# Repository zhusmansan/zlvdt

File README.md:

# Микроконтроллерный (esp32) преобразователь LVDT -> modbus 

Устройство для считывания LVDT сигнала с линейного датчика перемещений и передачи данных по modbus.

## Железо

Схема усилителя в папке [zlvdt_pcb](./zlvdt_pcb). 
Kicad проект.

## Софт

ESP_IDF проект прошивки в папке [zlvdt_firmware](./zlvdt_firmware)

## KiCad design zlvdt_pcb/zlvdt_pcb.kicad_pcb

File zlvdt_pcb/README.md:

# Усилитель и прецизионный выпрямитель для LVDT сигнала.

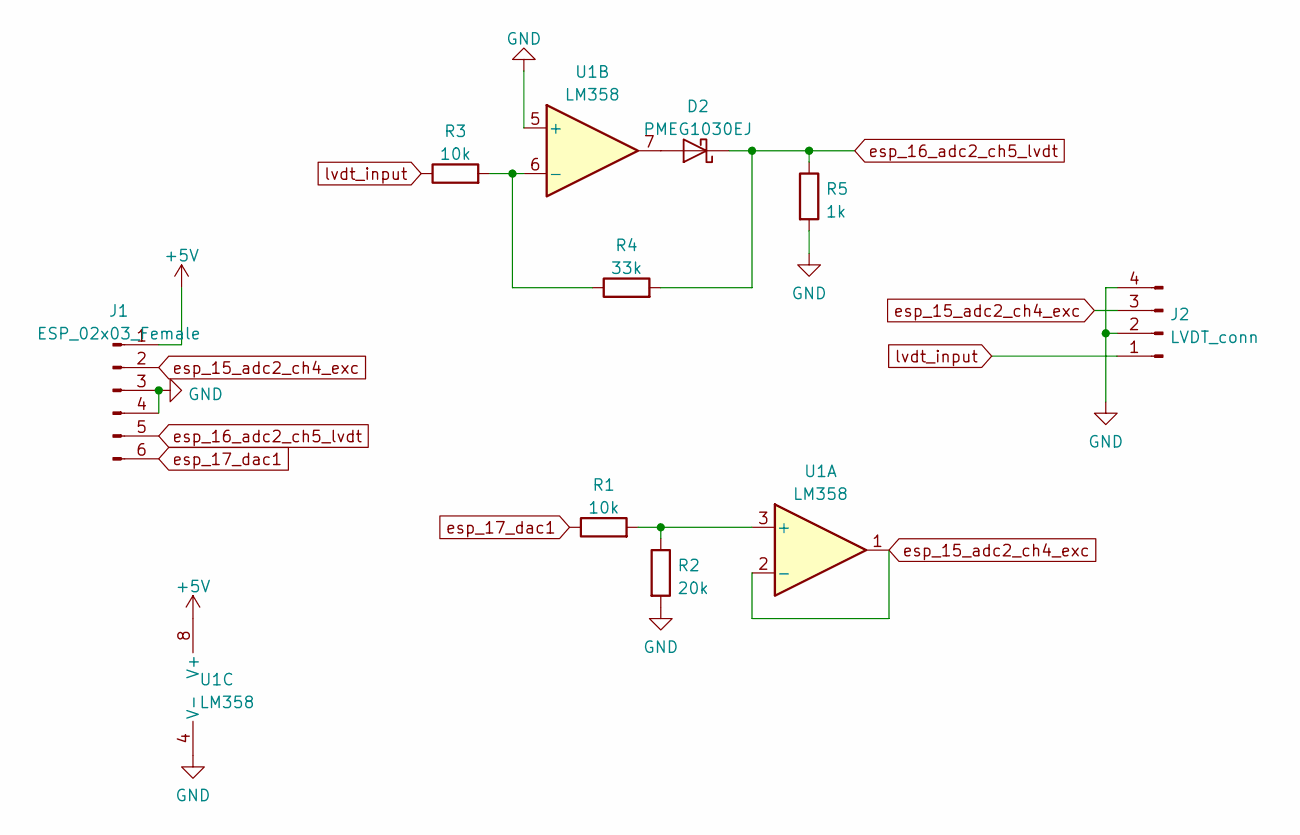
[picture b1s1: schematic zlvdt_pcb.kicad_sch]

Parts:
D2: PMEG1030EJ; D_SMA_Handsoldering
J1: ESP_02x03_Female; PinHeader_2x03_P2.54mm_Vertical
J2: LVDT_conn; PinHeader_2x02_P2.54mm_Vertical
R1, R3: 10k; R_0805_2012Metric
R2: 20k; R_0805_2012Metric
R4: 33k; R_0805_2012Metric
R5: 1k; R_0805_2012Metric
U1: LM358; DIP-8_W7.62mm

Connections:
+5V: J1.1, U1.8 (V+)
GND: J1.3, J1.4, J2.2, J2.4, R2.2, R5.2, U1.4 (V-), U1.5 (+)
unnamed: D2.2 (A), U1.7
unnamed: R1.2, R2.1, U1.3 (+)
unnamed: R3.2, R4.1, U1.6 (-)
esp_15_adc2_ch4_exc: J1.2, J2.3, U1.1, U1.2 (-)
esp_16_adc2_ch5_lvdt: D2.1 (K), J1.5, R4.2, R5.1
esp_17_dac1: J1.6, R1.1
lvdt_input: J2.1, R3.1

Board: 2 copper layers, 9 parts (6 on the bottom side), 9 nets, no tracks yet.

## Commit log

2024-05-15 Схема усилителя
2024-05-15 Софт
2024-05-15 +ридми для схемы
2024-05-15 Минорные изменения
2024-05-15 Плата переразведена топором
2024-05-15 Орфография
2025-04-18 test version
